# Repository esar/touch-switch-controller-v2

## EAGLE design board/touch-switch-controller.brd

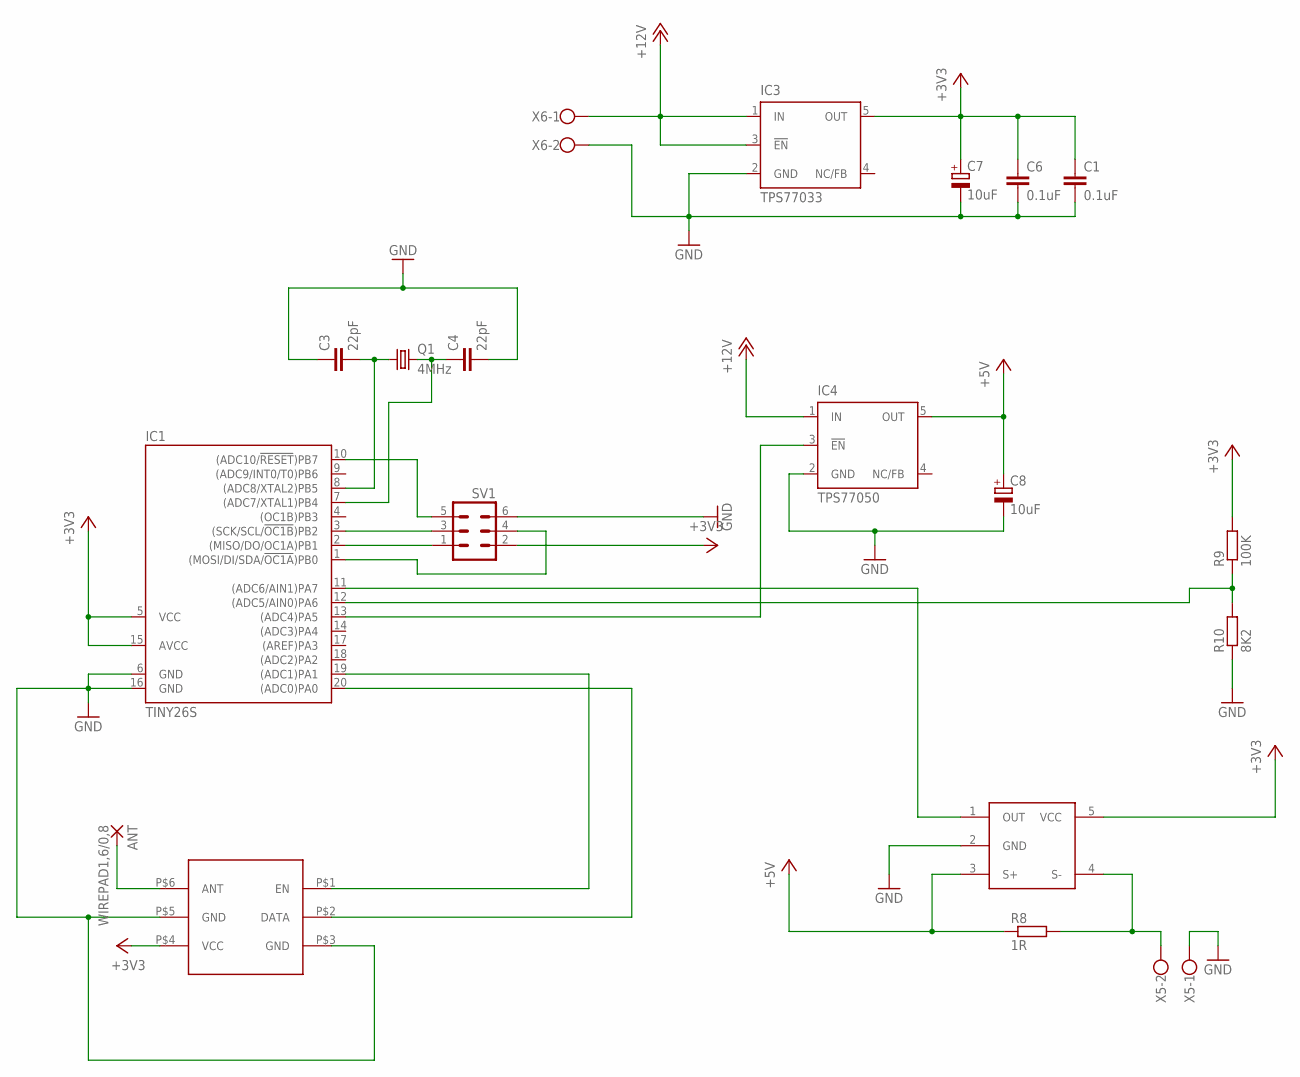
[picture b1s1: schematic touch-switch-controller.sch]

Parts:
ANT: WIREPAD1,6/0,8; 1,6/0,8
C1, C6: 0.1uF; C0603
C3, C4: 22pF; C0603
C7, C8: 10uF; SMC_B
IC1: TINY26S; SO20L
IC3: TPS77033; SOT23-DBV
IC4: TPS77050; SOT23-DBV
Q1: 4MHz; HC49UP
R8: 1R; R0603
R9: 100K; R0603
R10: 8K2; R0603
SV1: MA03-2
U$1: ZXCT1086; SOT23-5L
U$2: RTFQ1
X5, X6: W237-102

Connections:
+3V3: C1.1, C6.1, C7.+, IC1.5 (VCC), IC1.15 (AVCC), IC3.5 (OUT), R9.2, SV1.2, U$1.5 (VCC), U$2.P$4 (VCC)
+5V: C8.+, IC4.5 (OUT), R8.1, U$1.3 (S+)
+12V: IC3.1 (IN), IC3.3 (!EN), IC4.1 (IN), X6.1
GND: C1.2, C3.1, C4.2, C6.2, C7.-, C8.-, IC1.6 (GND), IC1.16 (GND), IC3.2 (GND), IC4.2 (GND), R10.1, SV1.6, U$1.2 (GND), U$2.P$3 (GND), U$2.P$5 (GND), X5.1, X6.2
unnamed: IC1.12 ((ADC5/AIN0)PA6), R9.1, R10.2
unnamed: IC1.19 ((ADC1)PA1), U$2.P$1 (EN)
unnamed: ANT.1, U$2.P$6 (ANT)
unnamed: IC1.13 ((ADC4)PA5), IC4.3 (!EN)
unnamed: IC1.2 ((MISO/DO/OC1A)PB1), SV1.1
unnamed: IC1.3 ((SCK/SCL/!OC1B!)PB2), SV1.3
unnamed: IC1.10 ((ADC10/!RESET!)PB7), SV1.5
unnamed: IC1.1 ((MOSI/DI/SDA/!OC1A!)PB0), SV1.4
unnamed: IC1.20 ((ADC0)PA0), U$2.P$2 (DATA)
unnamed: R8.2, U$1.4 (S-), X5.2
unnamed: IC1.11 ((ADC6/AIN1)PA7), U$1.1 (OUT)
unnamed: C3.2, IC1.8 ((ADC8/XTAL2)PB5), Q1.1
unnamed: C4.1, IC1.7 ((ADC7/XTAL1)PB4), Q1.2

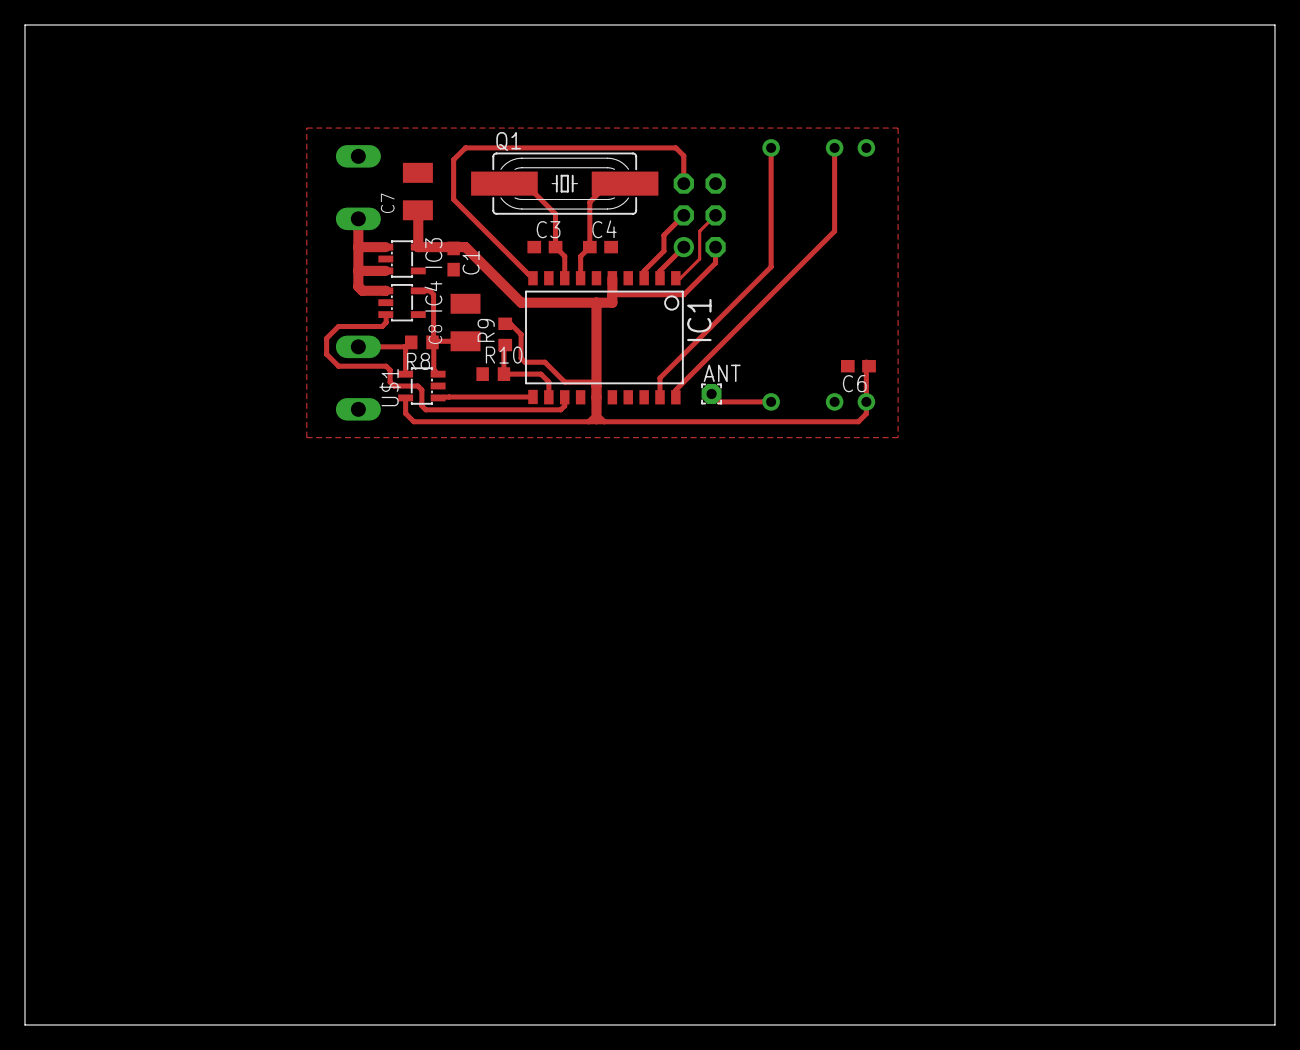
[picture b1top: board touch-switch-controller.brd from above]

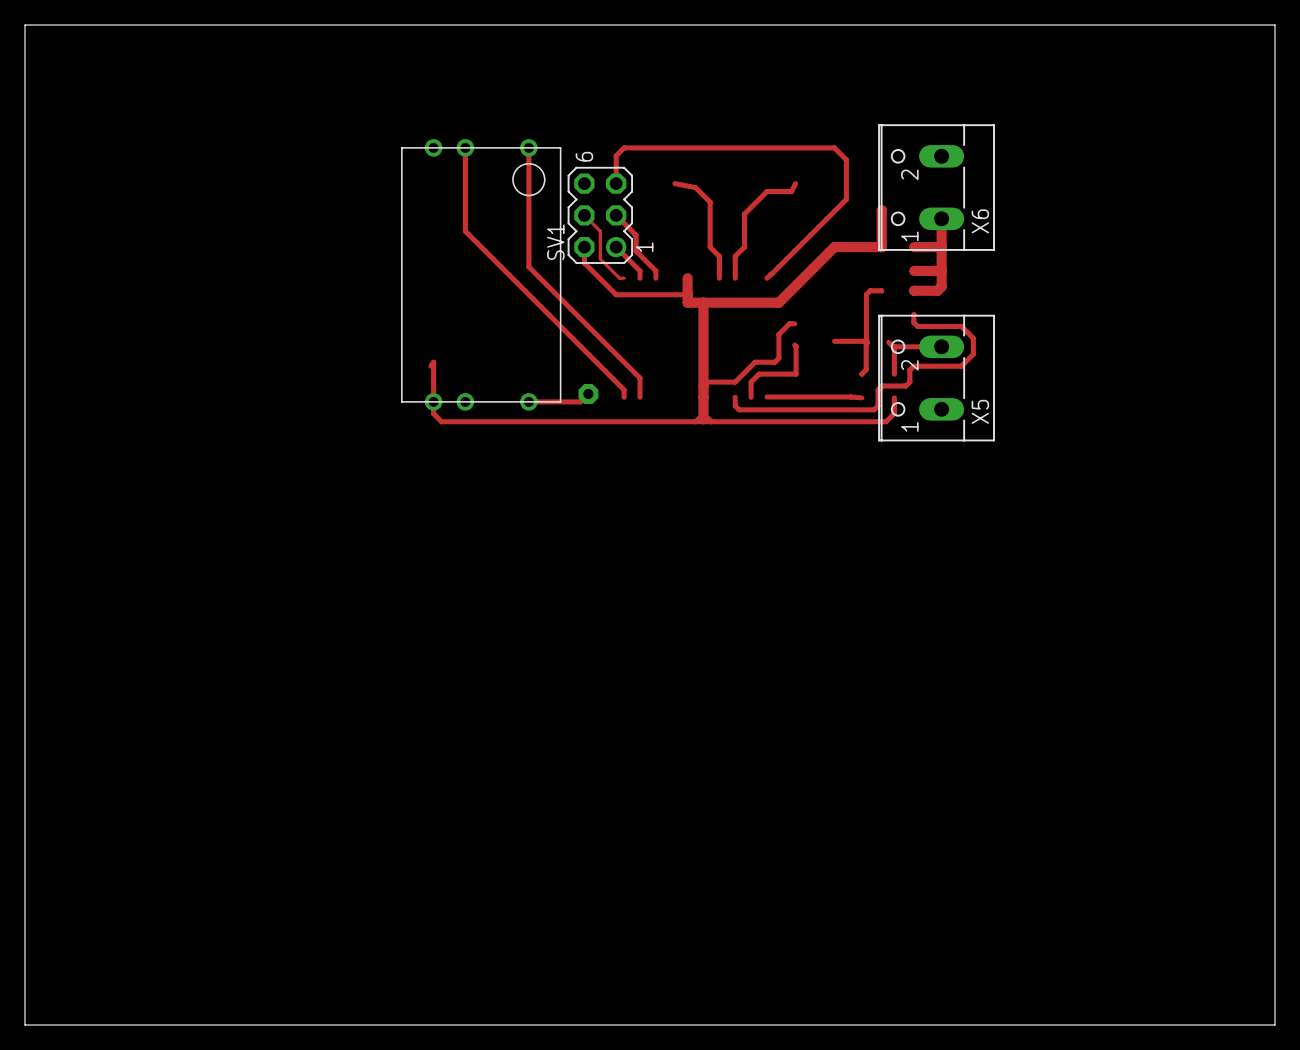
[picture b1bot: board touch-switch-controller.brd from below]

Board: 2 copper layers, 100.0 x 80.0 mm, 19 parts (4 on the bottom side), 17 nets.
